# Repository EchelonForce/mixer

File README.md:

# Eurorack Mixer Module

This the KiCAD design of a Eurorack mixer module with 4 inputs.

Full writeup here: https://www.robotdialogs.com/2022/09/eurorack-41-mixer-module.html

This work is licensed under a Creative Commons Attribution-NonCommercial-ShareAlike 4.0 International License. https://creativecommons.org/licenses/by-nc-sa/4.0/

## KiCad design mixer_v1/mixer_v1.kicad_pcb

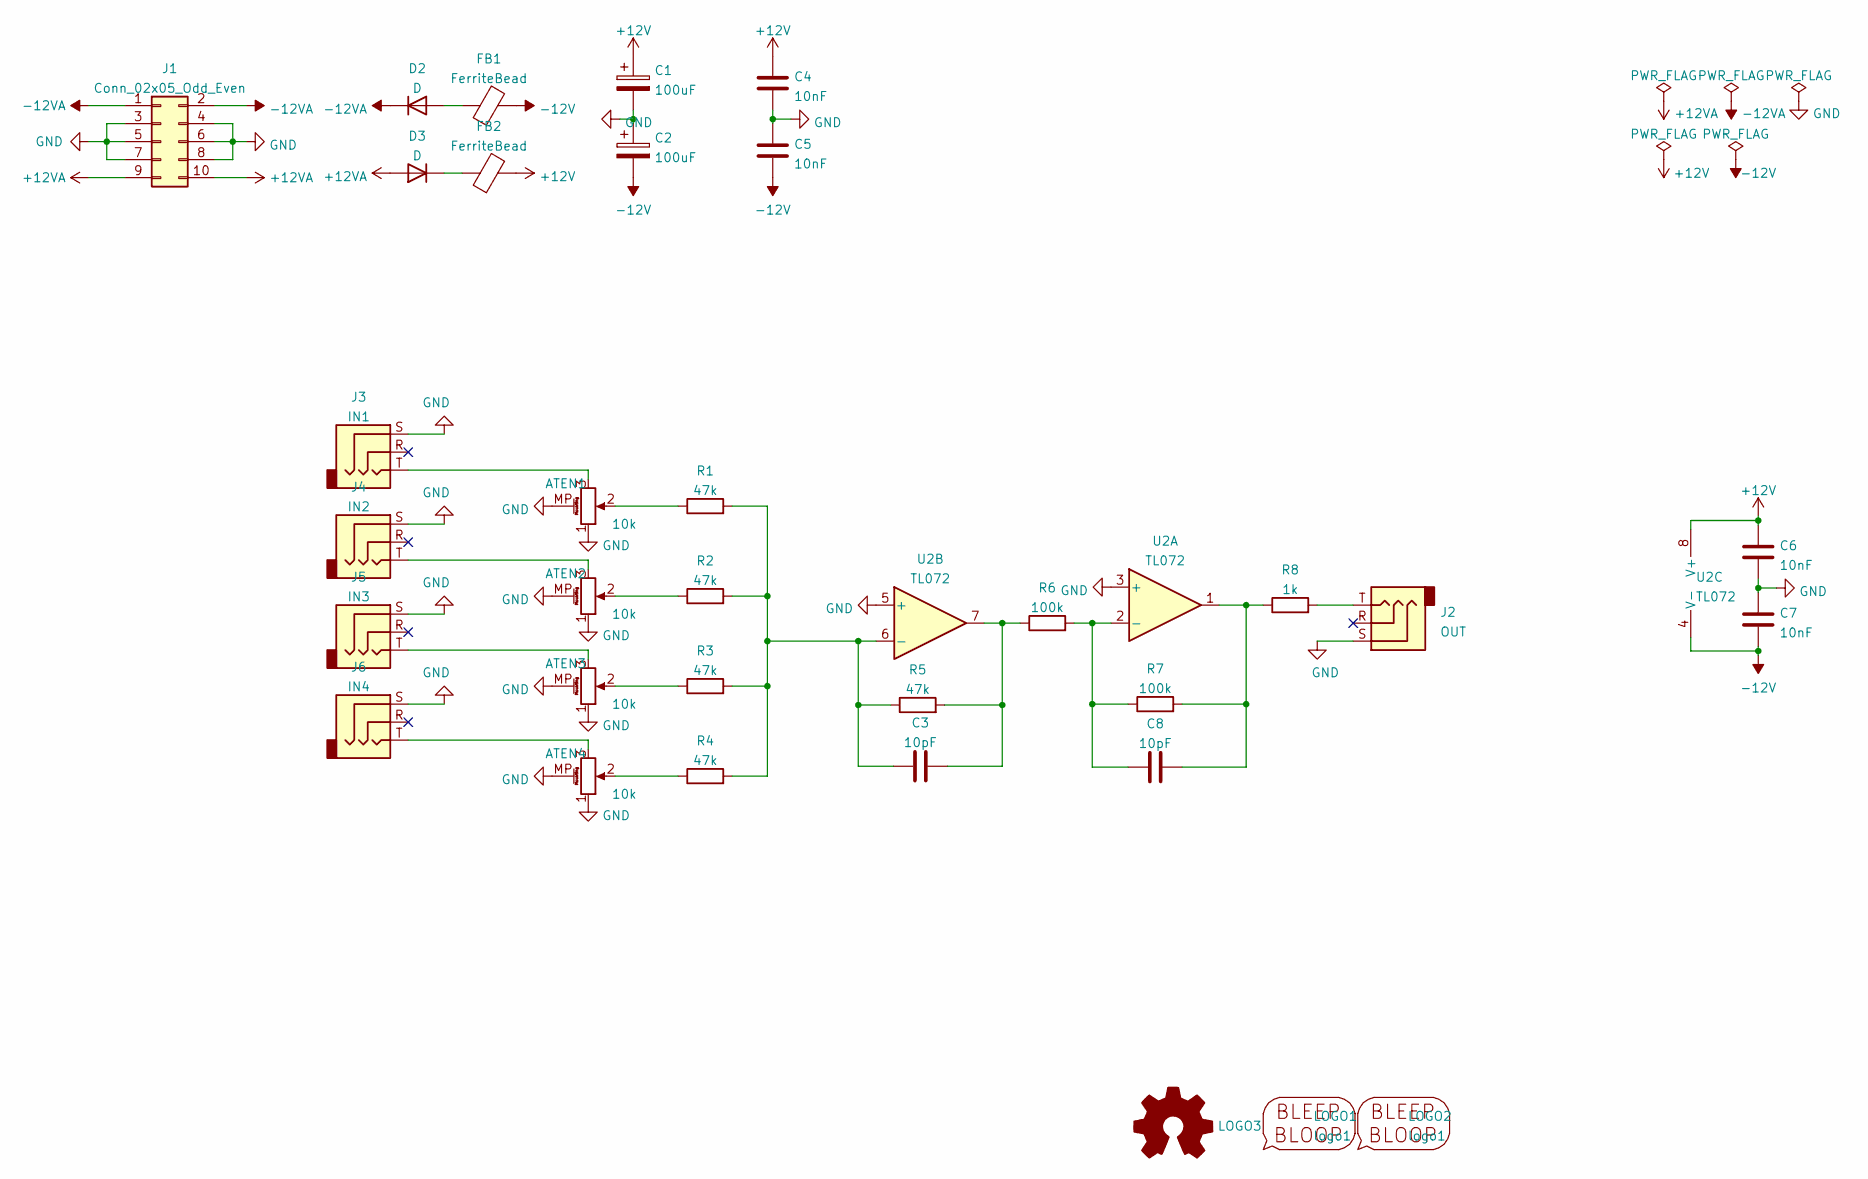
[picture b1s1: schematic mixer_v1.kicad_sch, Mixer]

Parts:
ATEN1, ATEN2, ATEN3, ATEN4: 10k; Potentiometer_Alpha_RD901F-40-00D_Single_Vertical_w_3d
C1, C2: 100uF; CP_Radial_D5.0mm_P2.50mm
C3, C8: 10pF; C_1206_3216Metric_Pad1.33x1.80mm_HandSolder
C4, C5, C6, C7: 10nF; C_1206_3216Metric_Pad1.33x1.80mm_HandSolder
D2, D3: D; D_A-405_P2.54mm_Vertical_KathodeUp
FB1, FB2: FerriteBead; L_Axial_L6.6mm_D2.7mm_P2.54mm_Vertical_Vishay_IM-2
J1: Conn_02x05_Odd_Even; IDC-Header_2x05_P2.54mm_Vertical
J2: OUT; Jack_3.5mm_MJ-355W_Vertical
J3: IN1; Jack_3.5mm_MJ-355W_Vertical
J4: IN2; Jack_3.5mm_MJ-355W_Vertical
J5: IN3; Jack_3.5mm_MJ-355W_Vertical
J6: IN4; Jack_3.5mm_MJ-355W_Vertical
LOGO1: logo1; Logo1
LOGO2: logo1; Logo2
LOGO3: Logo_Open_Hardware_Small; OSHW-Symbol_6.7x6mm_SilkScreen
R1, R2, R3, R4, R5: 47k; R_1206_3216Metric_Pad1.30x1.75mm_HandSolder
R6, R7: 100k; R_1206_3216Metric_Pad1.30x1.75mm_HandSolder
R8: 1k; R_1206_3216Metric_Pad1.30x1.75mm_HandSolder
U2: TL072; DIP-8_W7.62mm_Socket_LongPads

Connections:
+12V: C1.1, C4.1, C6.1, FB2.2, U2.8 (V+)
+12VA: D3.2 (A), J1.9, J1.10
-12V: C2.2, C5.2, C7.2, FB1.2, U2.4 (V-)
-12VA: D2.1 (K), J1.1, J1.2
GND: ATEN1.1, ATEN1.MP (MountPin), ATEN2.1, ATEN2.MP (MountPin), ATEN3.1, ATEN3.MP (MountPin), ATEN4.1, ATEN4.MP (MountPin), C1.2, C2.1, C4.2, C5.1, C6.2, C7.1, J1.3, J1.4, J1.5, J1.6, J1.7, J1.8, J2.S, J3.S, J4.S, J5.S, J6.S, U2.3 (+), U2.5 (+)
unnamed: ATEN1.2, R1.1
unnamed: ATEN1.3, J3.T
unnamed: ATEN2.2, R2.1
unnamed: ATEN3.2, R3.1
unnamed: ATEN3.3, J5.T
unnamed: ATEN4.2, R4.1
unnamed: ATEN4.3, J6.T
unnamed: D2.2 (A), FB1.1
unnamed: D3.1 (K), FB2.1
unnamed: J2.T, R8.2
unnamed: ATEN2.3, J4.T
unnamed: C8.2, R7.2, R8.1, U2.1
unnamed: C8.1, R6.2, R7.1, U2.2 (-)
unnamed: C3.1, R1.2, R2.2, R3.2, R4.2, R5.1, U2.6 (-)
unnamed: C3.2, R5.2, R6.1, U2.7

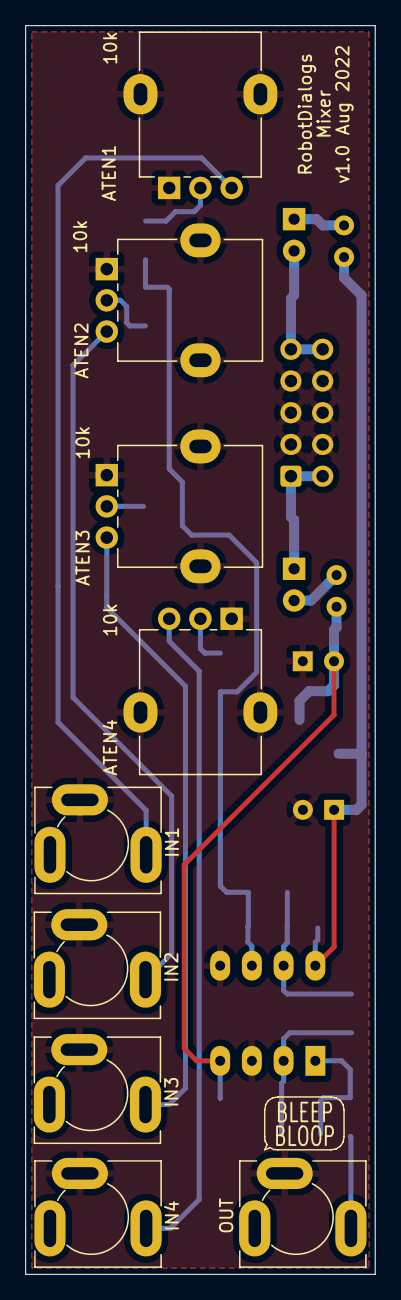
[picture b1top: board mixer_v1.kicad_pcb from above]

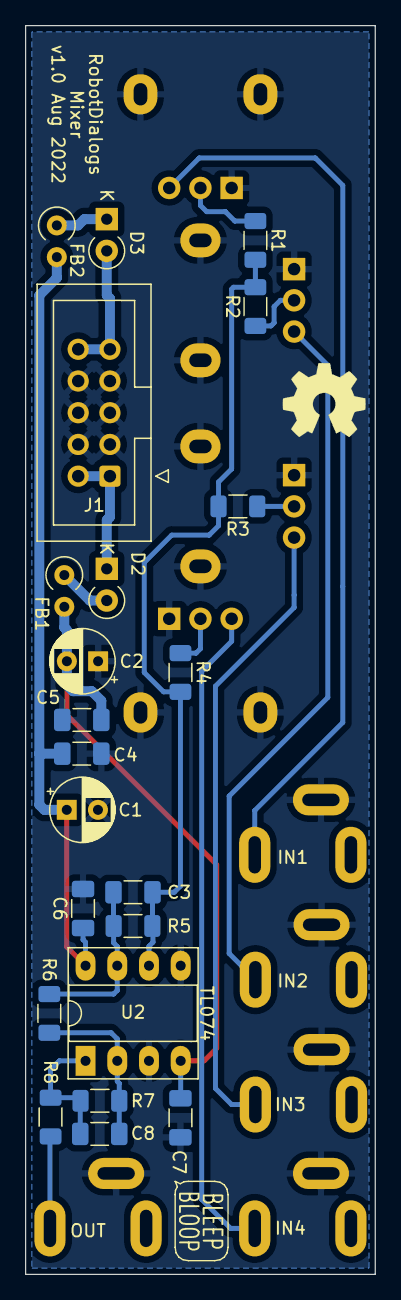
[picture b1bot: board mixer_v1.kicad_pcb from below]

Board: 2 copper layers, 28.0 x 100.0 mm, 34 parts (23 on the bottom side), 20 nets.

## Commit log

2022-08-06 Initial commit with .gitignore
2022-08-10 Schematic and PCB v1.0
2022-09-10 Panelized v1 version for production
2022-09-10 Front Panel design files
2022-09-10 Notes, pdfs and readme
